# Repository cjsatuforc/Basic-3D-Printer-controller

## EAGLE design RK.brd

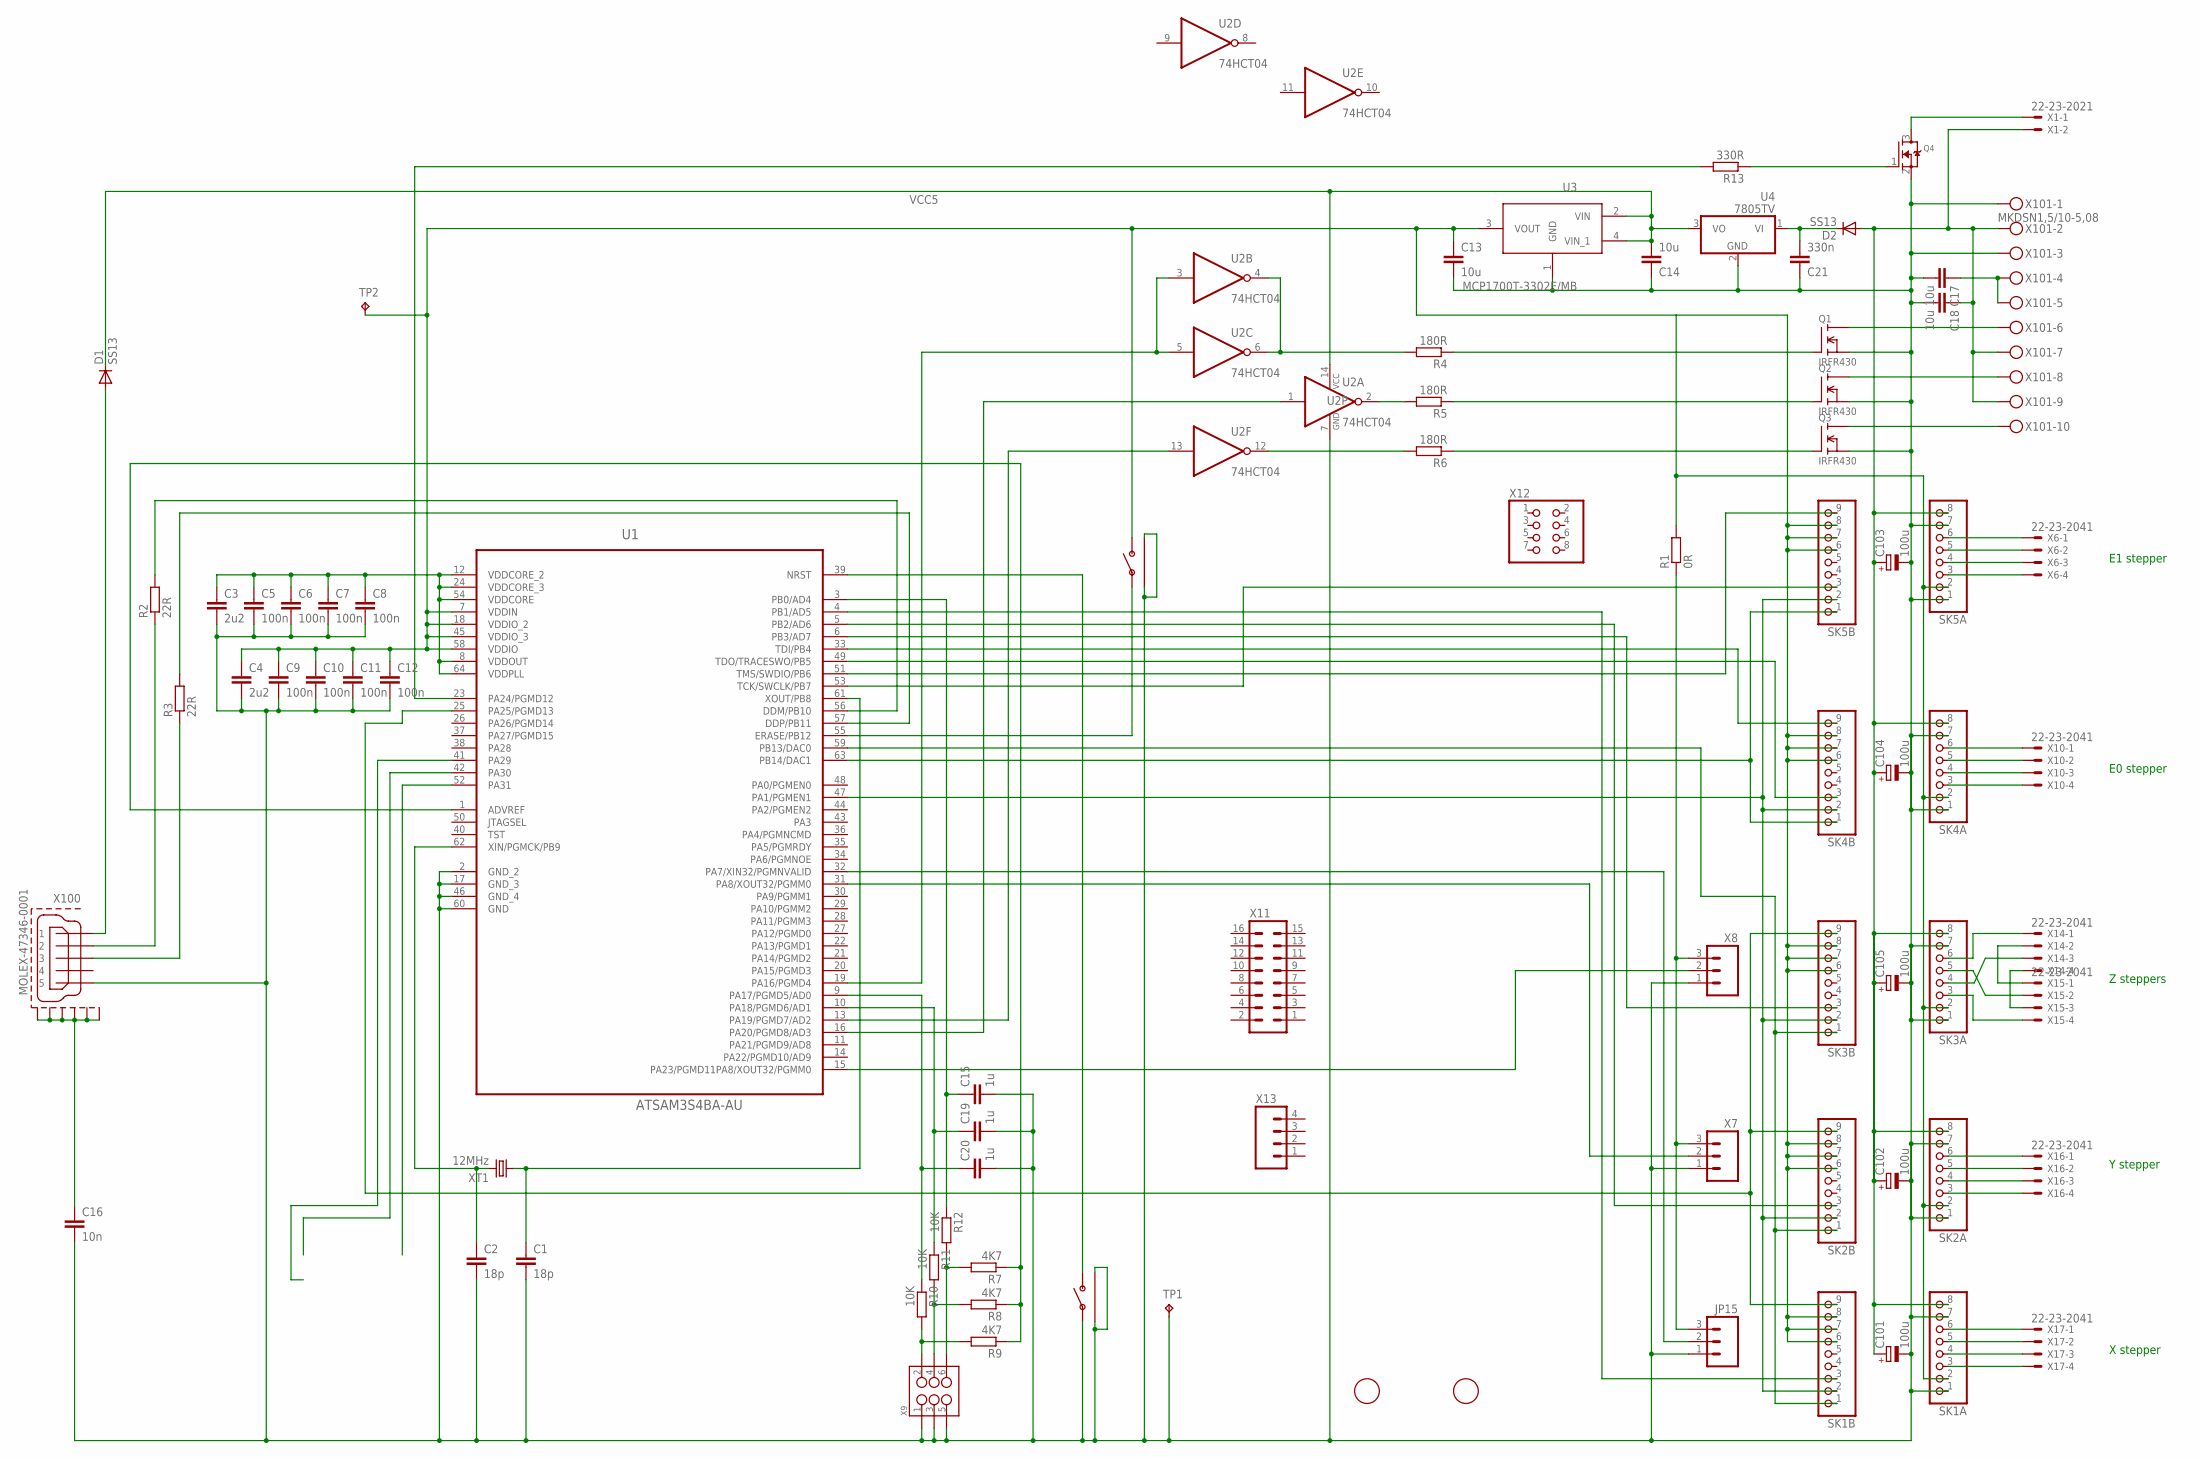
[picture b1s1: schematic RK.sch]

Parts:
C1, C2: 18p; C0603
C3, C4: 2u2; C0603
C5, C6, C7, C8, C9, C10, C11, C12: 100n; C0603
C13, C14: 10u; C0805
C15, C19, C20: 1u; C0603
C16: 10n; C0603
C17, C18: 10u; C0805K
C21: 330n; C0805
C101, C102, C103, C104, C105: 100u; PANASONIC_D
D1, D2: SS13; DO214AC
JP15: M03PTH; 1X03
Q1, Q2, Q3: IRFR430; DPAK
Q4: MOSFET-NREFLOW; SOT23
R1: 0R; R0603
R2, R3: 22R; R0603
R4, R5, R6: 180R; R0603
R7, R8, R9: 4K7; R0603
R10, R11, R12: 10K; R0603
R13: 330R; R0603
SK1A, SK2A, SK3A, SK4A, SK5A: PINHD-1X8BIG; 1X08-BIG
SK1B, SK2B, SK3B, SK4B, SK5B: PINHD-1X9; 1X09-BIG
TP1, TP2: TPPAD1-10; P1-10
U1: ATSAM3S4BA-AU; QFP50P1200X1200X160-64N
U2: 74HCT04; TSSOP14
U3: MCP1700T-3302E/MB; SOT150P400X160-4N
U4: 7805TV; TO220V
U$1, U$2: FIDUCIAL; FIDUCIAL_1MM
U$3, U$4: ALPS-SKHHLUA010; SKHHLUA010
X1: 22-23-2021
X6, X10, X14, X15, X16, X17: 22-23-2041
X7, X8: M03PTH; 1X03
X9: M03X22X3_SILK_SM; 2X3
X11: MA08-2
X12: PINHD-2X4; 2X04
X13: M04PTH; 1X04
X100: MOLEX-47346-0001; MOLEX-47364-0001
X101: MKDSN1,5/10-5,08
XT1: 12MHz; HC49U-V

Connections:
BED-VE: Q1.2 (D), X101.6
GND: C1.2, C2.2, C3.2, C4.2, C5.2, C6.2, C7.2, C8.2, C9.2, C10.2, C11.2, C12.2, C13.2, C14.1, C15.2, C16.2, C17.2, C18.2, C19.2, C20.2, C21.1, C101.-, C102.-, C103.-, C104.-, C105.-, JP15.1, Q1.3 (S), Q2.3 (S), Q3.3 (S), Q4.2 (S), SK1A.1, SK1A.7, SK2A.1, SK2A.7, SK3A.1, SK3A.7, SK4A.1, SK4A.7, SK5A.1, SK5A.7, TP1.TP, U1.2 (GND_2), U1.17 (GND_3), U1.46 (GND_4), U1.60 (GND), U2.7 (GND), U3.1 (GND), U4.2 (GND), U$3.P$1, U$3.P$3, U$3.P$4, U$4.P$3, U$4.P$4, X7.1, X8.1, X9.1, X9.3, X9.5, X100.5, X101.1, X101.3
HEATER1-VE: Q2.2 (D), X101.8
HEATER2-VE: Q3.2 (D), X101.10
unnamed: SK1B.2, SK2B.2, SK3B.2, SK4B.2, SK5B.2, U1.47 (PA1/PGMEN1)
unnamed: SK4A.3, X10.4
unnamed: SK4A.4, X10.3
unnamed: SK4A.5, X10.2
unnamed: SK4A.6, X10.1
unnamed: SK1A.3, X17.4
unnamed: SK1A.4, X17.3
unnamed: SK1A.5, X17.2
unnamed: SK1A.6, X17.1
unnamed: SK3A.6, X14.1
unnamed: SK3A.4, X14.3
unnamed: SK3A.3, X15.4
unnamed: X14.2, X15.1
unnamed: X14.4, X15.3
unnamed: SK3A.5, X15.2
unnamed: C18.1, C101.+, C102.+, C103.+, C104.+, C105.+, D2.A, SK1A.8, SK2A.8, SK3A.8, SK4A.8, SK5A.8, X1.2, X101.2, X101.7, X101.9
unnamed: SK5A.3, X6.4
unnamed: R2.2, U1.56 (DDM/PB10)
unnamed: SK5A.4, X6.3
unnamed: SK5A.5, X6.2
unnamed: C1.1, U1.61 (XOUT/PB8), XT1.1
unnamed: C2.1, U1.62 (XIN/PGMCK/PB9), XT1.2
unnamed: U1.55 (ERASE/PB12), U$4.P$1
unnamed: U1.39 (NRST), U$3.P$2
unnamed: SK1B.3, U1.4 (PB1/AD5)
unnamed: C20.1, R10.1, U1.9 (PA17/PGMD5/AD0)
unnamed: R3.2, U1.57 (DDP/PB11)
unnamed: U1.19 (PA16/PGMD4), U2.3 (I), U2.5 (I)
unnamed: U1.13 (PA19/PGMD7/AD2), U2.13 (I)
unnamed: D1.A, X100.1
unnamed: R2.1, X100.2
unnamed: R7.2, R12.2, X9.6
unnamed: R3.1, X100.3
unnamed: R13.2, U1.23 (PA24/PGMD12)
unnamed: SK5A.6, X6.1
unnamed: SK2A.3, X16.4
unnamed: SK2A.4, X16.3
unnamed: SK2A.5, X16.2
unnamed: SK1B.9, SK2B.9, SK3B.9, U1.25 (PA25/PGMD13)
unnamed: SK2A.6, X16.1
unnamed: SK5B.3, U1.53 (TCK/SWCLK/PB7)
unnamed: JP15.3, R1.1, X7.3, X8.3
unnamed: C16.1, X100.GND1, X100.GND2, X100.GND3, X100.GND4, X100.GND5, X100.GND6
unnamed: SK4B.9, U1.33 (TDI/PB4)
unnamed: C17.1, X101.4, X101.5
unnamed: C19.1, R11.1, U1.10 (PA18/PGMD6/AD1)
unnamed: SK4B.1, SK5B.1, U1.63 (PB14/DAC1)
unnamed: SK1B.1, SK2B.1, SK3B.1, U1.59 (PB13/DAC0)
unnamed: R7.1, R8.1, R9.1, U1.1 (ADVREF)
unnamed: SK4B.3, U1.49 (TDO/TRACESWO/PB5)
unnamed: R8.2, R11.2, X9.4
unnamed: SK5B.9, U1.51 (TMS/SWDIO/PB6)
unnamed: SK3B.3, U1.6 (PB3/AD7)
unnamed: SK2B.3, U1.5 (PB2/AD6)
unnamed: U1.15 (PA23/PGMD11PA8/XOUT32/PGMM0), X8.2
unnamed: Q4.3 (D), X1.1
unnamed: U1.31 (PA8/XOUT32/PGMM0), X7.2
unnamed: Q4.1 (G), R13.1
unnamed: Q1.1 (G), R4.1
unnamed: Q2.1 (G), R5.1
unnamed: Q3.1 (G), R6.1
unnamed: R9.2, R10.2, X9.2
unnamed: C15.1, R12.1, U1.3 (PB0/AD4)
unnamed: U1.16 (PA20/PGMD8/AD3), U2.1 (I)
unnamed: R6.2, U2.12 (O)
unnamed: R4.2, U2.4 (O), U2.6 (O)
unnamed: R5.2, U2.2 (O)
unnamed: C21.2, D2.C, U4.1 (VI)
VCC: C4.1, C9.1, C10.1, C11.1, C12.1, C13.1, R1.2, SK1A.2, SK1B.6, SK1B.7, SK1B.8, SK2A.2, SK2B.6, SK2B.7, SK2B.8, SK3A.2, SK3B.6, SK3B.7, SK3B.8, SK4A.2, SK4B.6, SK4B.7, SK4B.8, SK5A.2, SK5B.6, SK5B.7, SK5B.8, TP2.TP, U1.7 (VDDIN), U1.18 (VDDIO_2), U1.45 (VDDIO_3), U1.58 (VDDIO), U3.3 (VOUT), U$4.P$2
VCC5: C14.2, D1.C, U2.14 (VCC), U3.2 (VIN), U3.4 (VIN_1), U4.3 (VO)
VDDCORE: C3.1, C5.1, C6.1, C7.1, C8.1, U1.8 (VDDOUT), U1.12 (VDDCORE_2), U1.24 (VDDCORE_3), U1.54 (VDDCORE), U1.64 (VDDPLL)
X6: JP15.2, U1.32 (PA7/XIN32/PGMNVALID)

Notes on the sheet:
Z steppers
E0 stepper
E1 stepper
Y stepper
X stepper

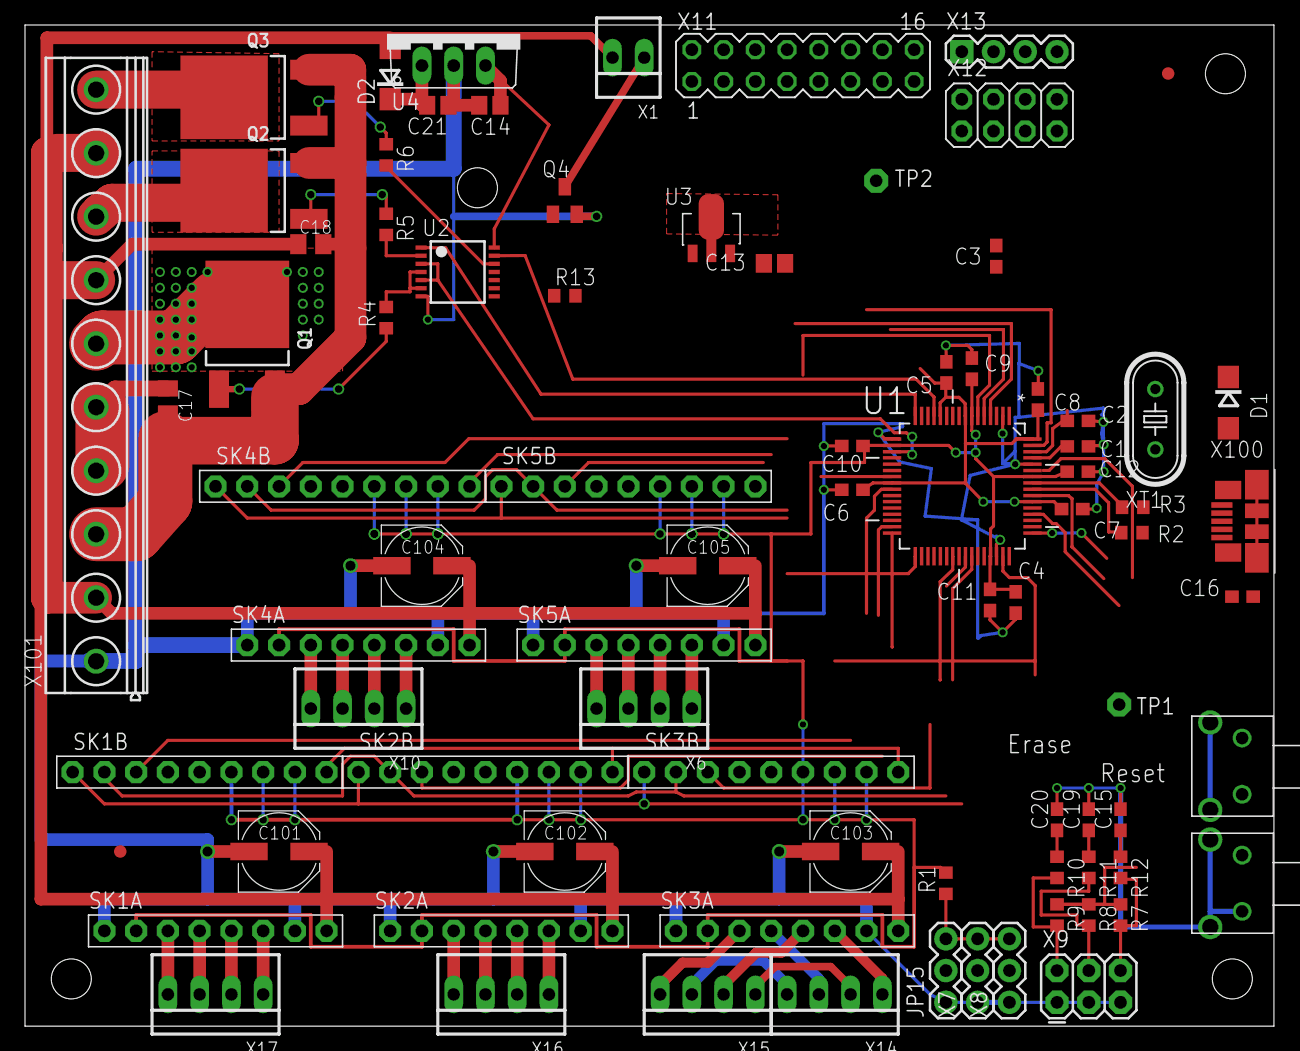
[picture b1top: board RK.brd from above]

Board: 2 copper layers, 100.0 x 80.1 mm, 82 parts (0 on the bottom side), 76 nets.

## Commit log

2016-02-21 :tada: Added .gitattributes & .gitignore files
2016-02-21 First public commit
2016-02-21 Clarified PCB specification
2016-02-21 Minor corrections to BOM file
2016-02-21 Added project notes file

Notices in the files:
parts and their libraries:
SparkFun-Connectors: Licensing: CC v3.0 Share-Alike You are welcome to use this library for commercial purposes.
